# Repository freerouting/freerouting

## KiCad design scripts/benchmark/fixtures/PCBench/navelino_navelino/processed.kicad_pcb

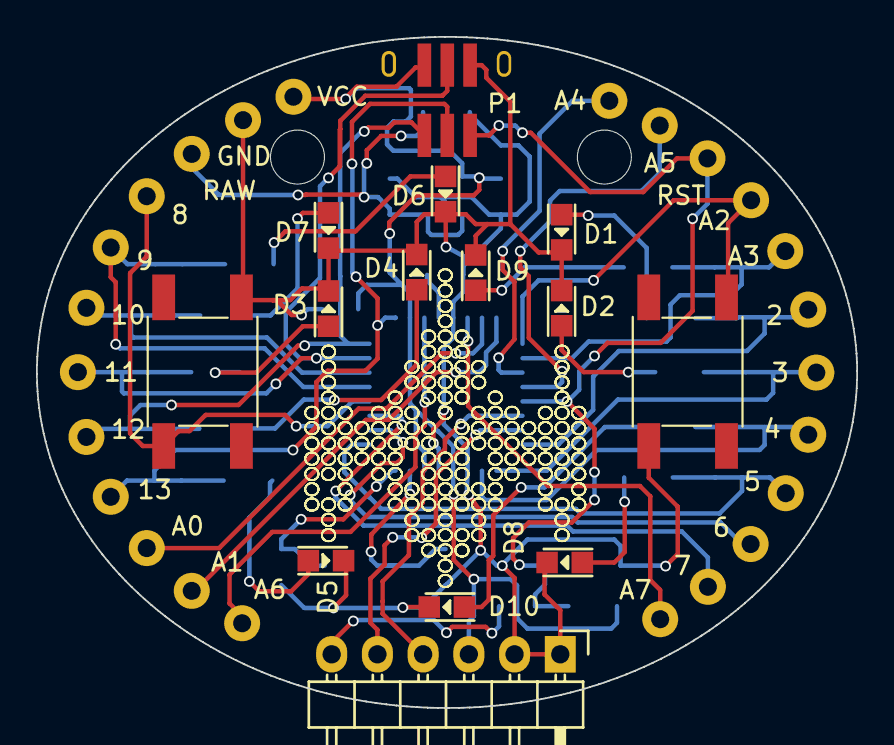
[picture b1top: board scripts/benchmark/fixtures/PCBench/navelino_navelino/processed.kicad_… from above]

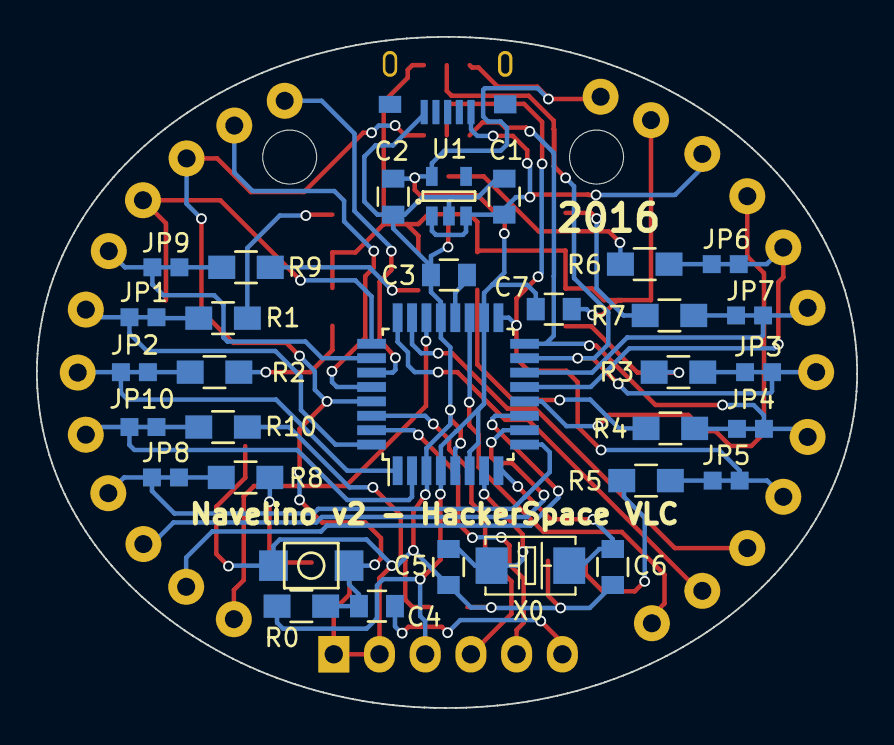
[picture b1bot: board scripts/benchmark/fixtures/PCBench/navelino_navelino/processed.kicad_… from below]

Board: 2 copper layers, 45.6 x 37.3 mm, 73 parts (33 on the bottom side), 50 nets.

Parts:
2, 3, 4, 5, 6, 7, 8, 9, 10, 11, 12, 13: CONN_1; SolderWirePad_single_1mmDrill
A0, A1, A2, A3, A4, A5, A6, A7: CONN_1; SolderWirePad_single_1mmDrill
C1, C3, C4, C7: 0.1uF; C_0805
C2: 1uF; C_0805
C5, C6: 27pF; C_0805
CON1: USB; ST-USB-001G
D1, D2, D3: BLUE; LED-0805
D4, D5, D6, D7, D8, D9, D10: LED; LED-0805
GND: CONN_1; SolderWirePad_single_1mmDrill
IC1: ATMEGA328P-A; TQFP-32_7x7mm_Pitch0.8mm
JP1, JP2, JP3, JP4, JP5, JP6, JP7, JP8, JP9, JP10: JUMPER; PCB_JUMPER
M1, M2: CONN_1; MountingHole_3mm
P1: CONN_02X03; ISPSMD
P3: CONN_6; Pin_Header_Angled_1x06
R0: 10K; R_0805_HandSoldering
R1, R2, R3, R4, R5, R6, R7, R8, R9, R10: 330; R_0805_HandSoldering
RAW: CONN_1; SolderWirePad_single_1mmDrill
RST: CONN_1; SolderWirePad_single_1mmDrill
SW0: SW_PUSH; B3U-1000P
SW1, SW2: SMD-SWITCH-TACTILE-SPST-NO(4P-D6.0MM); SW4-SMD-6.0X6.0X5.0MM
U1: XC6204B332MR; SOT-23-5
VCC: CONN_1; SolderWirePad_single_1mmDrill
X0: CRYSTAL; X2-SMD-5.0X3.2X1.3MM

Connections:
A6: A6.1, IC1.19
A7: A7.1, IC1.22
DTR: C4.2, P3.6
GND: C1.2, C2.2, C3.2, C5.1, C6.1, C7.2, CON1.5, D1.2, D2.2, D3.2, D4.2, D5.2, D6.2, D7.2, D8.2, D9.2, D10.2, GND.1, IC1.3, IC1.5, IC1.21, P1.6, P3.1, P3.2, SW0.2, SW1.3, SW2.3, U1.2
unnamed: C3.1, IC1.20
unnamed: D1.1, R1.2
unnamed: D2.1, R2.2
unnamed: D3.1, R3.2
unnamed: D4.1, R4.2
unnamed: D5.1, R5.2
unnamed: D6.1, R6.2
unnamed: D7.1, R7.2
unnamed: D8.1, R8.2
unnamed: D9.1, R9.2
unnamed: D10.1, R10.2
unnamed: JP1.2, R1.1
unnamed: JP2.2, R2.1
unnamed: JP3.2, R3.1
unnamed: JP4.2, R4.1
unnamed: JP5.2, R5.1
unnamed: JP6.2, R6.1
unnamed: JP7.2, R7.1
unnamed: JP8.2, R8.1
unnamed: JP9.2, R9.1
unnamed: JP10.2, R10.1
PB0: 8.1, IC1.12, SW2.1
PB1: 9.1, IC1.13, JP6.1
PB2: 10.1, IC1.14, JP7.1
PB3/MOSI: 11.1, IC1.15, JP3.1, P1.4
PB4/MISO: 12.1, IC1.16, JP4.1, P1.1
PB5/SCK: 13.1, IC1.17, JP5.1, P1.3
PC0: A0.1, IC1.23
PC1: A1.1, IC1.24
PC2: A2.1, IC1.25, SW1.1
PC3: A3.1, IC1.26, JP9.1
PD2: 2.1, IC1.32, JP1.1
PD3: 3.1, IC1.1, JP2.1
PD4: 4.1, IC1.2, JP10.1
PD5: 5.1, IC1.9, JP8.1
PD6: 6.1, IC1.10
PD7: 7.1, IC1.11
RAW: C1.1, CON1.1, RAW.1, U1.1, U1.3
RESET: C4.1, IC1.29, P1.5, R0.1, RST.1, SW0.1
RXI: IC1.30, P3.4
SCL: A5.1, IC1.28
SDA: A4.1, IC1.27
TXO: IC1.31, P3.5
VCC: C2.1, C7.1, IC1.4, IC1.6, IC1.18, P1.2, P3.3, R0.2, U1.5, VCC.1
XTAL1: C5.2, IC1.7, X0.1
XTAL2: C6.2, IC1.8, X0.2

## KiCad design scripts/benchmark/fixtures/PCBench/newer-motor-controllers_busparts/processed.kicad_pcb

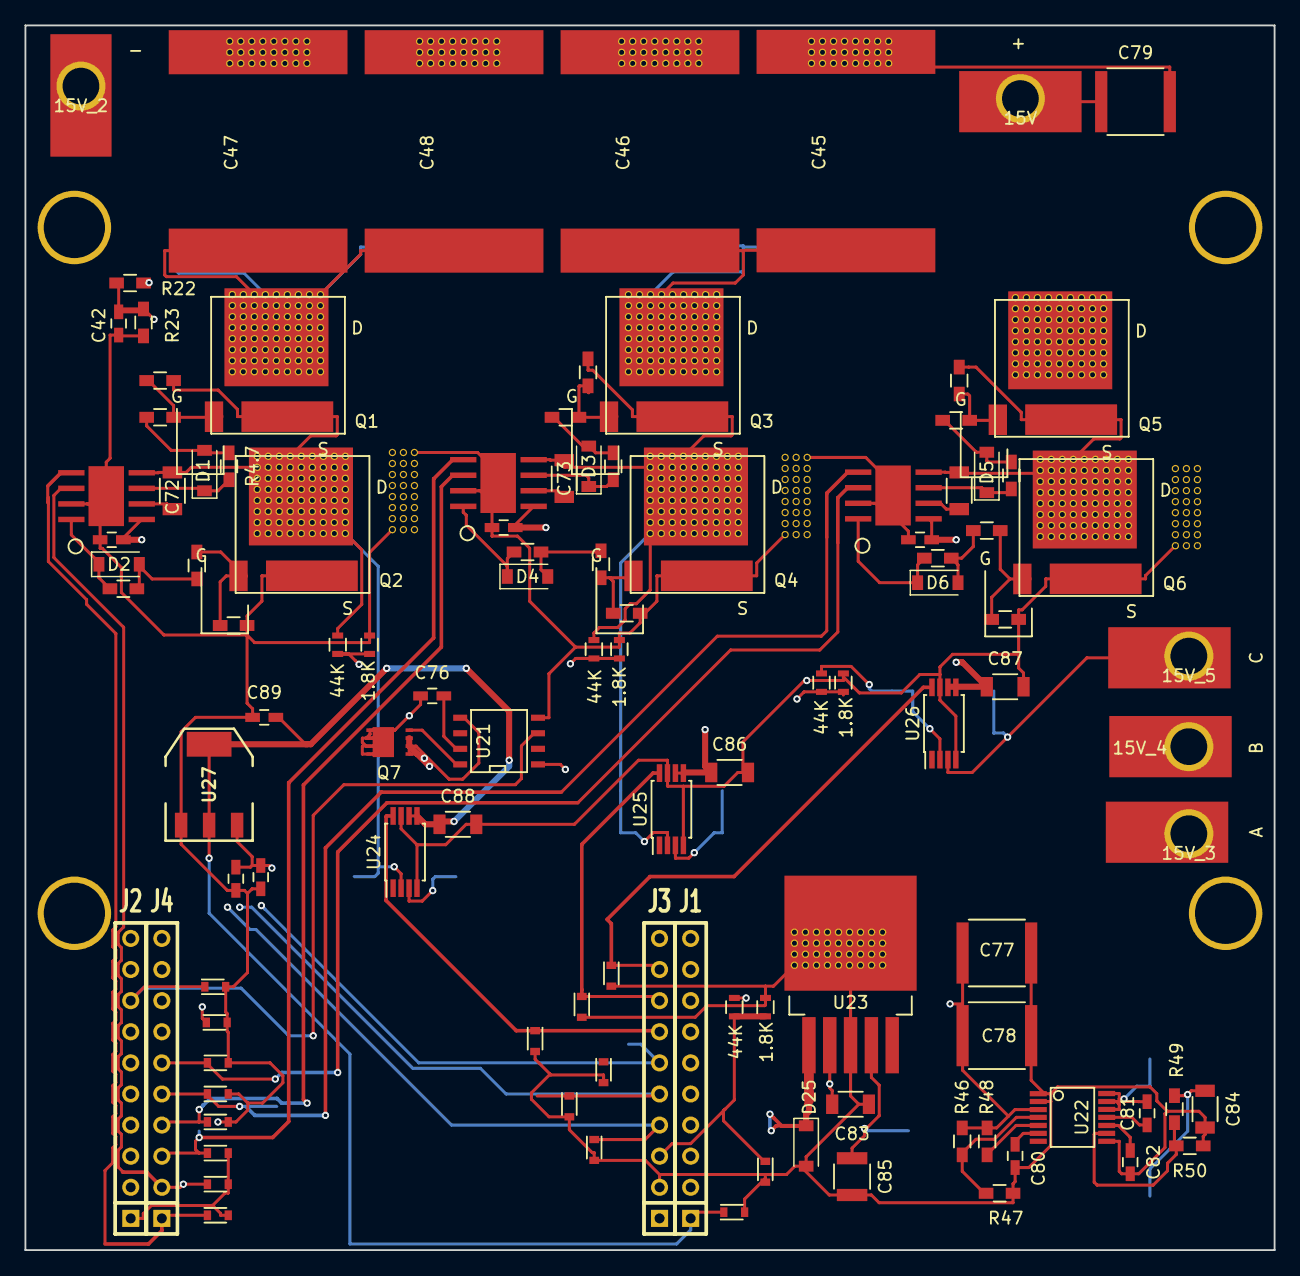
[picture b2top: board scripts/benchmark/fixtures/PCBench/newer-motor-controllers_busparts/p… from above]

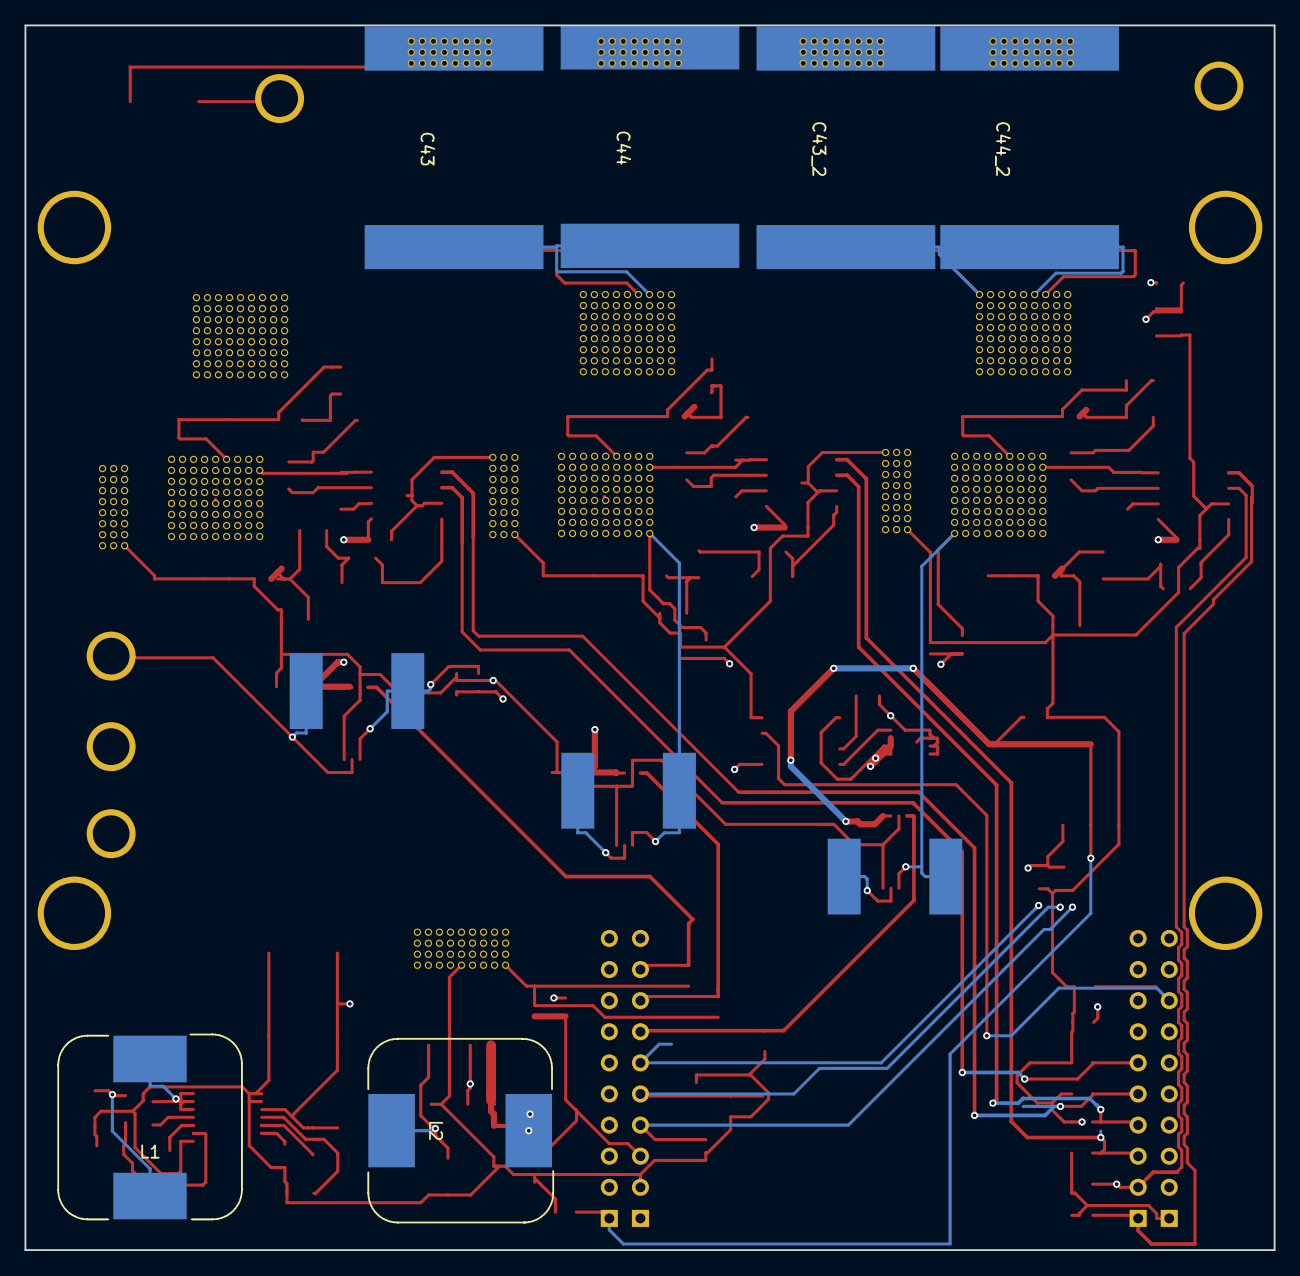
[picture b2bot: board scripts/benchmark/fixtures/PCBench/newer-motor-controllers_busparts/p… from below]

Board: 4 copper layers, 102.0 x 100.0 mm, 123 parts (9 on the bottom side), 58 nets.

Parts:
10k1, 10k2, 10k3, 10k4, 10k5, 10k6: R_Small; R_0603_HandSoldering
15V, 15V_2, 15V_3, 15V_4, 15V_5: via
+: V+; SolderWirePad_single_SMD_5x10mm
-: V-; SolderWirePad_single_SMD_5x10mm
A: motor_A; SolderWirePad_single_SMD_5x10mm
B: motor_B; SolderWirePad_single_SMD_5x10mm
C: motor_C; SolderWirePad_single_SMD_5x10mm
C42: 2.2uf; C_0603_HandSoldering
C43, C43_2, C44, C44_2, C45, C46, C47, C48: 4.7uf; cap_6065
C69, C70, C71, C82, C89: 1uf; C_0603_HandSoldering
C72, C73, C74, C86, C87, C88: 0.1uf; C_1206
C75: 0.1uf; C_0603_HandSoldering
C76: 10pf; C_0603_HandSoldering
C77, C78, C79: 1uf 250V; C_2220
C80: 22nf; C_0603_HandSoldering
C81: 10nf; C_0603_HandSoldering
C83, C84: 10uf; C_1206
C85: 100uf; C_1210
C90: 10uf; C_0603_HandSoldering
D1, D2, D3, D4, D5, D6: D_Schottky_Small; SOD-123
D8, D9, D10, D11, D12, D13, D14, D15, D16, D17, D18, D19, D20, D21, D22, D23: TVS; D_0603
D25: D_Schottky; SOD-123
J1: Ti_Booster_40_J1; SIL-10J1
J2: Ti_Booster_40_J2; SIL-10J2
J3: Ti_Booster_40_J3; SIL-10J3
J4: Ti_Booster_40_J4; SIL-10J4
L1, L2: INDUCTOR; MSS1583-154KED
Q1, Q2, Q3, Q4, Q5, Q6: FDMT-800; P-PG-HSOF-08
Q7: Q_NMOS_DSG; VSONP-8
R4.1, R4.2, R4.3, R4.4, R4.5, R4.7: R_Small; R_0603_HandSoldering
R22: NTC 10k; R_0603_HandSoldering
R23: 10k; R_0603_HandSoldering
R40, R41, R42, R42_2: 1.8K; R_0603
R43, R44, R45, R45_2: 44K; R_0603
R46: 75k; R_0603_HandSoldering
R47: 4.42k; R_0603_HandSoldering
R48: 499k; R_0603_HandSoldering
R49: 13k; R_0603_HandSoldering
R50: 2k; R_0603_HandSoldering
R51, R52, R53: 0.001R; SHUNT_CSS2H-3920
U18, U19, U20: UCC27210; SO_PowerPAD-8
U21: Si8751; SOIC-8-N
U22: LM5161; SSOP-14
U23: LM2595; TO-263-5Lead
U24, U25, U26: INA240; TSSOP-8_4.4x3mm_Pitch0.65mm
U27: NCP1117ST33T3G; SOT-223
ferrite1, ferrite2, ferrite3, ferrite4, ferrite5, ferrite6: R_Small; R_0603_HandSoldering

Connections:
+5V: C75.1, C85.1, C90.1, J3.1, L2.2, U21.1, U23.4, U27.3
+15V: C76.1, C83.1, C84.1, L1.2, Q7.1, R49.1, U23.2
/Ti_120vgate/vsense_a: D12.1, J3.4, R40.2, R43.2
/Ti_120vgate/vsense_b: D13.1, J3.5, R41.2, R44.2
/Ti_120vgate/vsense_c: J3.6, R42.2, R45.2
/VBUS: 15V.1, +.1, C43.2, C43_2.2, C44.2, C44_2.2, C45.2, C46.2, C47.2, C48.2, C77.1, C78.1, C79.1, Q1.1, Q3.1, Q5.1, R45_2.1, R46.1, R48.2, U22.3
/connector/CurrentA: D15.1, J3.7, U24.8
/connector/CurrentB: D16.1, J3.8, U25.8
/connector/CurrentC: D17.1, J3.9, U26.8
/connector/EN_GATE: D10.1, J2.8, U21.3
/connector/PWM_H1: D18.1, J4.1, U18.5
/connector/PWM_H2: D20.1, J4.3, U19.5
/connector/PWM_H3: D22.1, J4.5, U20.5
/connector/PWM_L1: D19.1, J4.2, U18.6
/connector/PWM_L2: D21.1, J4.4, U19.6
/connector/PWM_L3: D23.1, J4.6, U20.6
/connector/TEMP: C42.1, D8.1, J2.3, R22.2, R23.1
/connector/VBUS_sense: D11.1, J3.3, R42_2.2, R45_2.2
/current_sense_80v/PHASE_1: 15V_3.1, A.1, R53.1, U24.3
/current_sense_80v/PHASE_2: 15V_4.1, B.1, R52.1, U25.3
/current_sense_80v/PHASE_3: 15V_5.1, C.1, R51.1, U26.3
/mosfet/H1: D1.1, R4.7.2, U18.3
/mosfet/H2: D3.1, R4.2.2, U19.3
/mosfet/H3: D5.1, R4.4.2, U20.3
/mosfet/L1: D2.1, R4.1.2, U18.8
/mosfet/L2: D4.1, R4.3.2, U19.8
/mosfet/L3: D6.1, R4.5.2, U20.8
/mosfet/phase_a_in: 10k1.2, C72.1, Q1.2, Q2.1, R43.1, R53.2, U18.4, U24.2
/mosfet/phase_b_in: 10k3.2, C73.1, Q3.2, Q4.1, R44.1, R52.2, U19.4, U25.2
/mosfet/phase_c_in: 10k5.2, C74.1, Q5.2, Q6.1, R45.1, R51.2, U20.4, U26.2
GND: 10k2.2, 10k4.2, 10k6.2, 15V_2.1, -.1, C42.2, C43.1, C43_2.1, C44.1, C44_2.1, C45.1, C46.1, C47.1, C48.1, C69.2, C70.2, C71.2, C75.2, C77.2, C78.2, C79.2, C80.2, C82.2, C83.2, C84.2, C85.2, C86.2, C87.2, C88.2, C89.2, C90.2, D8.2, D9.2, D10.2, D11.2, D12.2, D13.2, D14.2, D15.2, D16.2, D17.2, D18.2, D19.2, D20.2, D21.2, D22.2, D23.2, D25.2, J2.1, J3.2, Q2.2, Q4.2, Q6.2, R23.2, R40.1, R41.1, R42.1, R42_2.1, R47.2, R50.2, U18.7, U18.pad, U19.7, U19.pad, U20.7, U20.pad, U21.4, U22.1, U22.2, U22.8, U23.3, U24.4, U24.7, U25.4, U25.7, U26.4, U26.7, U27.1
unnamed: 10k1.1, Q1.3, ferrite1.1
unnamed: 10k2.1, Q2.3, ferrite2.1
unnamed: 10k3.1, Q3.3, ferrite3.1
unnamed: 10k4.1, Q4.3, ferrite4.1
unnamed: 10k5.1, Q5.3, ferrite5.1
unnamed: 10k6.1, Q6.3, ferrite6.1
unnamed: C69.1, C70.1, C71.1, Q7.2, U18.1, U19.1, U20.1, U21.5
unnamed: C72.2, U18.2
unnamed: C73.2, U19.2
unnamed: C74.2, U20.2
unnamed: C76.2, U21.7
unnamed: C80.1, U22.6
unnamed: C81.1, L1.1, U22.12, U22.13, U22.14
unnamed: C81.2, U22.11
unnamed: C82.1, U22.10
unnamed: C86.1, C87.1, C88.1, C89.1, D9.1, J1.1, R22.1, U24.5, U24.6, U25.5, U25.6, U26.5, U26.6, U27.2
unnamed: D1.2, R4.7.1, ferrite1.2
unnamed: D2.2, R4.1.1, ferrite2.2
unnamed: D3.2, R4.2.1, ferrite3.2
unnamed: D4.2, R4.3.1, ferrite4.2
unnamed: D5.2, R4.4.1, ferrite5.2
unnamed: D6.2, R4.5.1, ferrite6.2
unnamed: D25.1, L2.1, U23.1
unnamed: Q7.3, U21.8
unnamed: R46.2, R47.1, U22.4
unnamed: R48.1, U22.5
unnamed: R49.2, R50.1, U22.9

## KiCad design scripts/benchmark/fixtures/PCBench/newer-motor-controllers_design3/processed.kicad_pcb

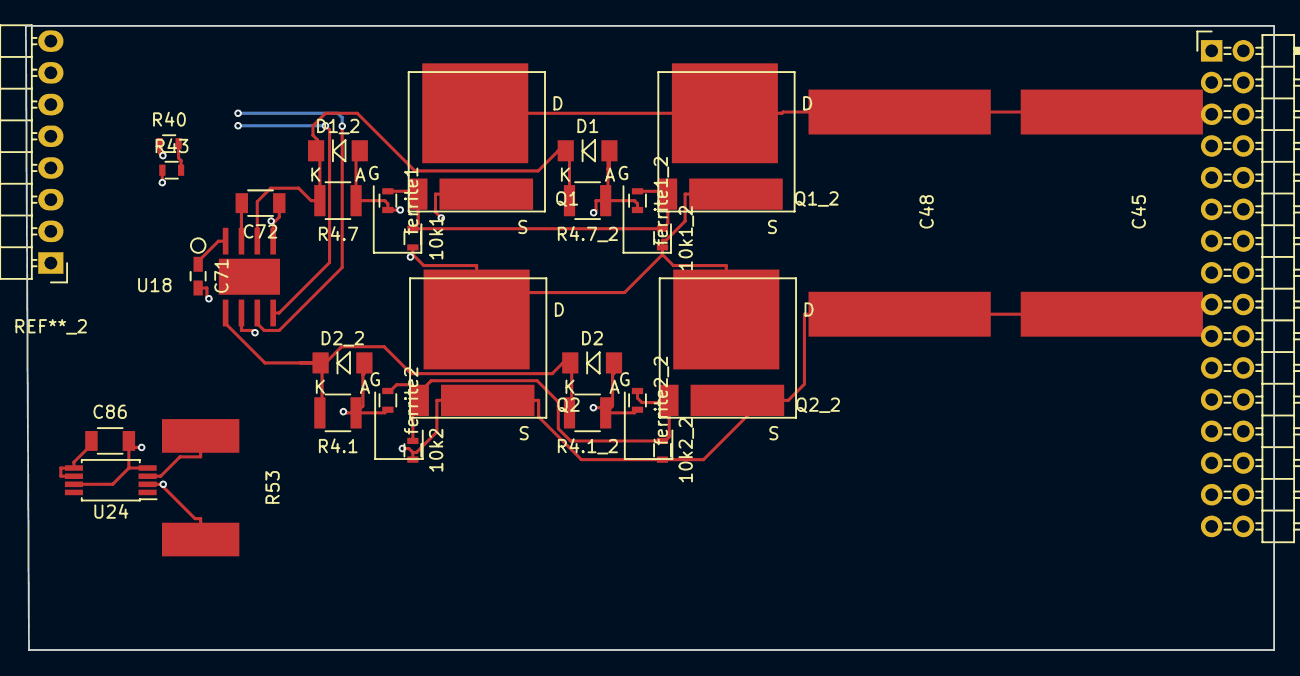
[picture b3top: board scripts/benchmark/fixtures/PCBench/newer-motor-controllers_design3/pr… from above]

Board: 4 copper layers, 100.0 x 50.0 mm, 30 parts (0 on the bottom side), 14 nets.

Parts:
10k1, 10k1_2, 10k2, 10k2_2: R_Small; R_0603
C45, C48: 4.7uf; cap_6065
C71: 1uf; C_0603_HandSoldering
C72, C86: 0.1uf; C_1206
D1, D1_2, D2, D2_2: D_Schottky_Small; MiniMELF_Standard
Q1, Q1_2, Q2, Q2_2: FDMT-800; P-PG-HSOF-08
R4.1, R4.1_2, R4.7, R4.7_2: R_Small; R_1210
R40: 1.8K; R_0603
R43: 39K; R_0603
R53: 0.001R; SHUNT_CSS2H-3920
U18: UCC27210; SO_PowerPAD-8
U24: INA240; TSSOP-8_4.4x3mm_Pitch0.65mm
ferrite1, ferrite1_2, ferrite2, ferrite2_2: R_Small; R_0603

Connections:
/Ti_120vgate/H1: D1.1, D1_2.1, R4.7.2, R4.7_2.2, U18.3
/Ti_120vgate/L1: D2.1, D2_2.1, R4.1.2, R4.1_2.2, U18.8
/Ti_120vgate/phase_a_in: 10k1.2, 10k1_2.2, C72.1, Q1.2, Q1_2.2, Q2.1, Q2_2.1, R43.1, R53.2, U18.4, U24.2
/connector/Vsense_a: R40.2, R43.2
/mosfet/VBUS: C45.2, C48.2, Q1.1, Q1_2.1
GND: 10k2.2, 10k2_2.2, C45.1, C48.1, C71.2, C86.2, Q2.2, Q2_2.2, R40.1, U18.7, U24.4, U24.7
unnamed: 10k1.1, 10k1_2.1, Q1.3, Q1_2.3, ferrite1.1, ferrite1_2.1
unnamed: 10k2.1, 10k2_2.1, Q2.3, Q2_2.3, ferrite2.1, ferrite2_2.1
unnamed: C71.1, U18.1
unnamed: C72.2, U18.2
unnamed: C86.1, U24.5, U24.6
unnamed: D1.2, D1_2.2, R4.7.1, R4.7_2.1, ferrite1.2, ferrite1_2.2
unnamed: D2.2, D2_2.2, R4.1.1, R4.1_2.1, ferrite2.2, ferrite2_2.2
unnamed: R53.1, U24.3
